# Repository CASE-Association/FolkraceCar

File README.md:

# CASE Folkrace Car - laZEr

## The 2020 Folkrace car project
 A car developed for the main focus of evaluationg, methos for producing a fun and educational car for the Robot SM Folkrace class.
 These are the main topics:
- Navigation
- Mapping/ localisation
- Electric design
- Cassis design
- Weight optimization

## Project Structure

## Placeholder

## System overview

## How do you use it?

## How does it work?

## Development

## Contributors

## License

Distributed under the MIT license. See ``LICENSE`` for more information.

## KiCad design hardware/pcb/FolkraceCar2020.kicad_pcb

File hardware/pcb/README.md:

## Notes for Folkrace PCB

### Bring up notes for REV 1-2

* eFuse does not work consistently - two have been broken - unclear why

#### Changes for next rev

* Add way to connect external 5V (protection for DC/DC)
* On off for 3V3 (complete rail)
* Move to edge-mounted buttons
* Check real width of screen (38 mm length)
* Reconnect fault LED to not be on when off
* Change to better switch for on/off operation
* Transient protection and possibly reverse current diode for eFuse
* Check if we can change to Molex nano fit connectors (both connectors oriented towards RP conn)
* Add 90 deg connector for start module
* Flip FAN connector so silkscreen looks good

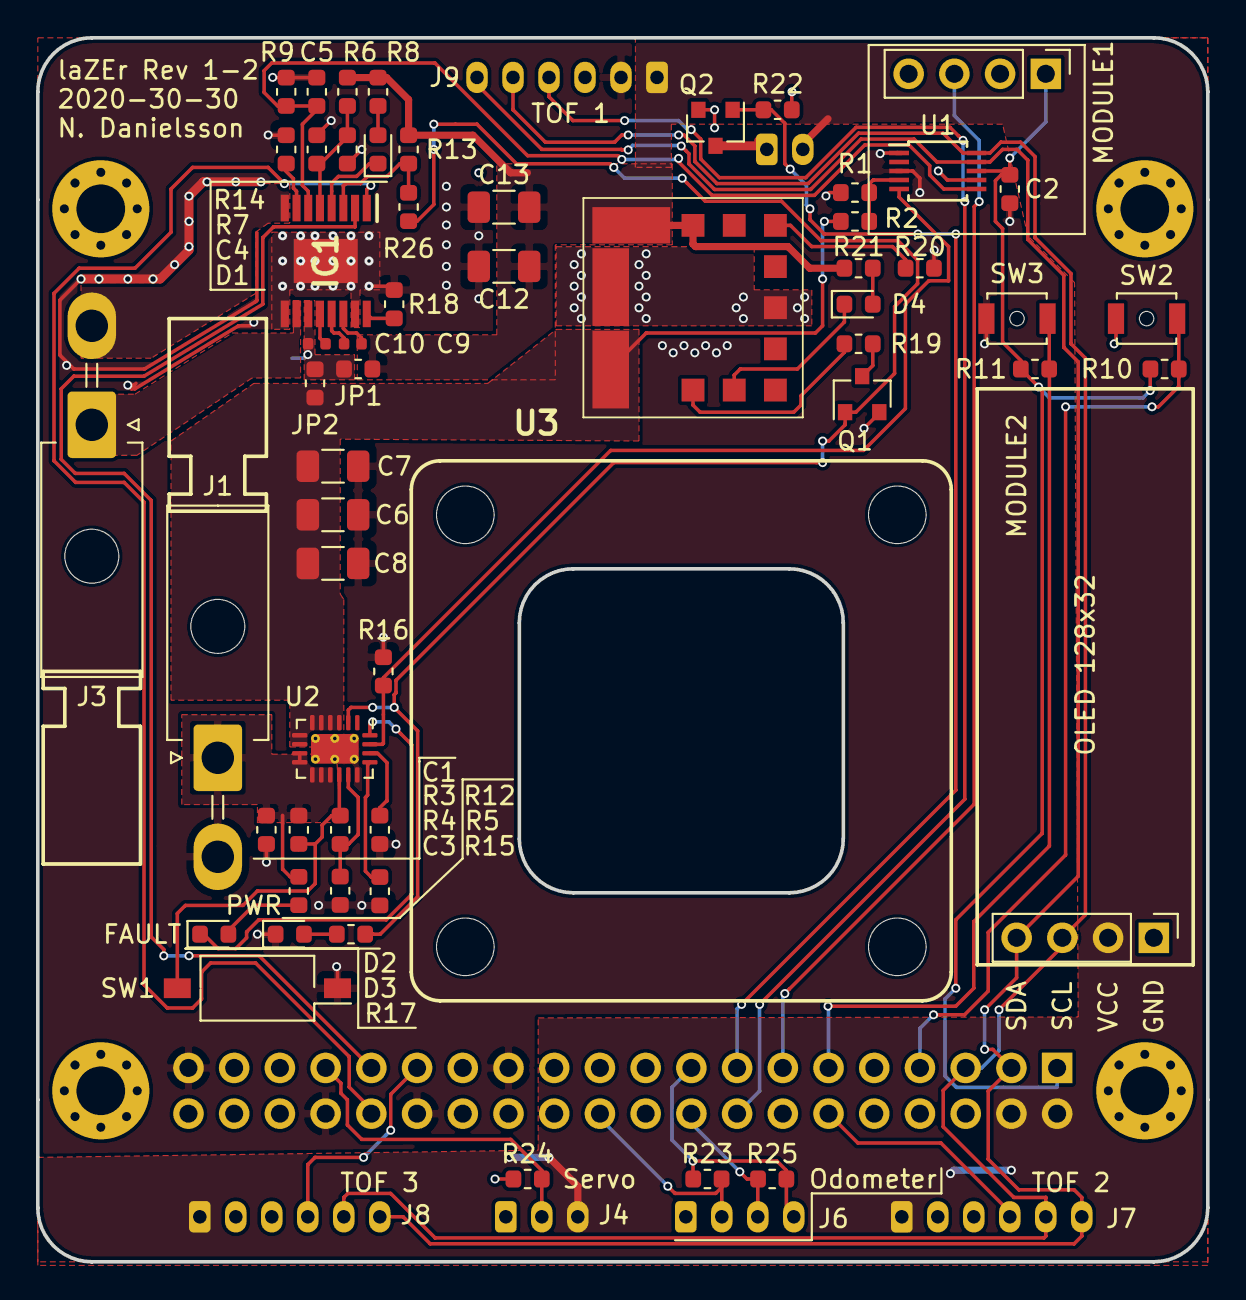
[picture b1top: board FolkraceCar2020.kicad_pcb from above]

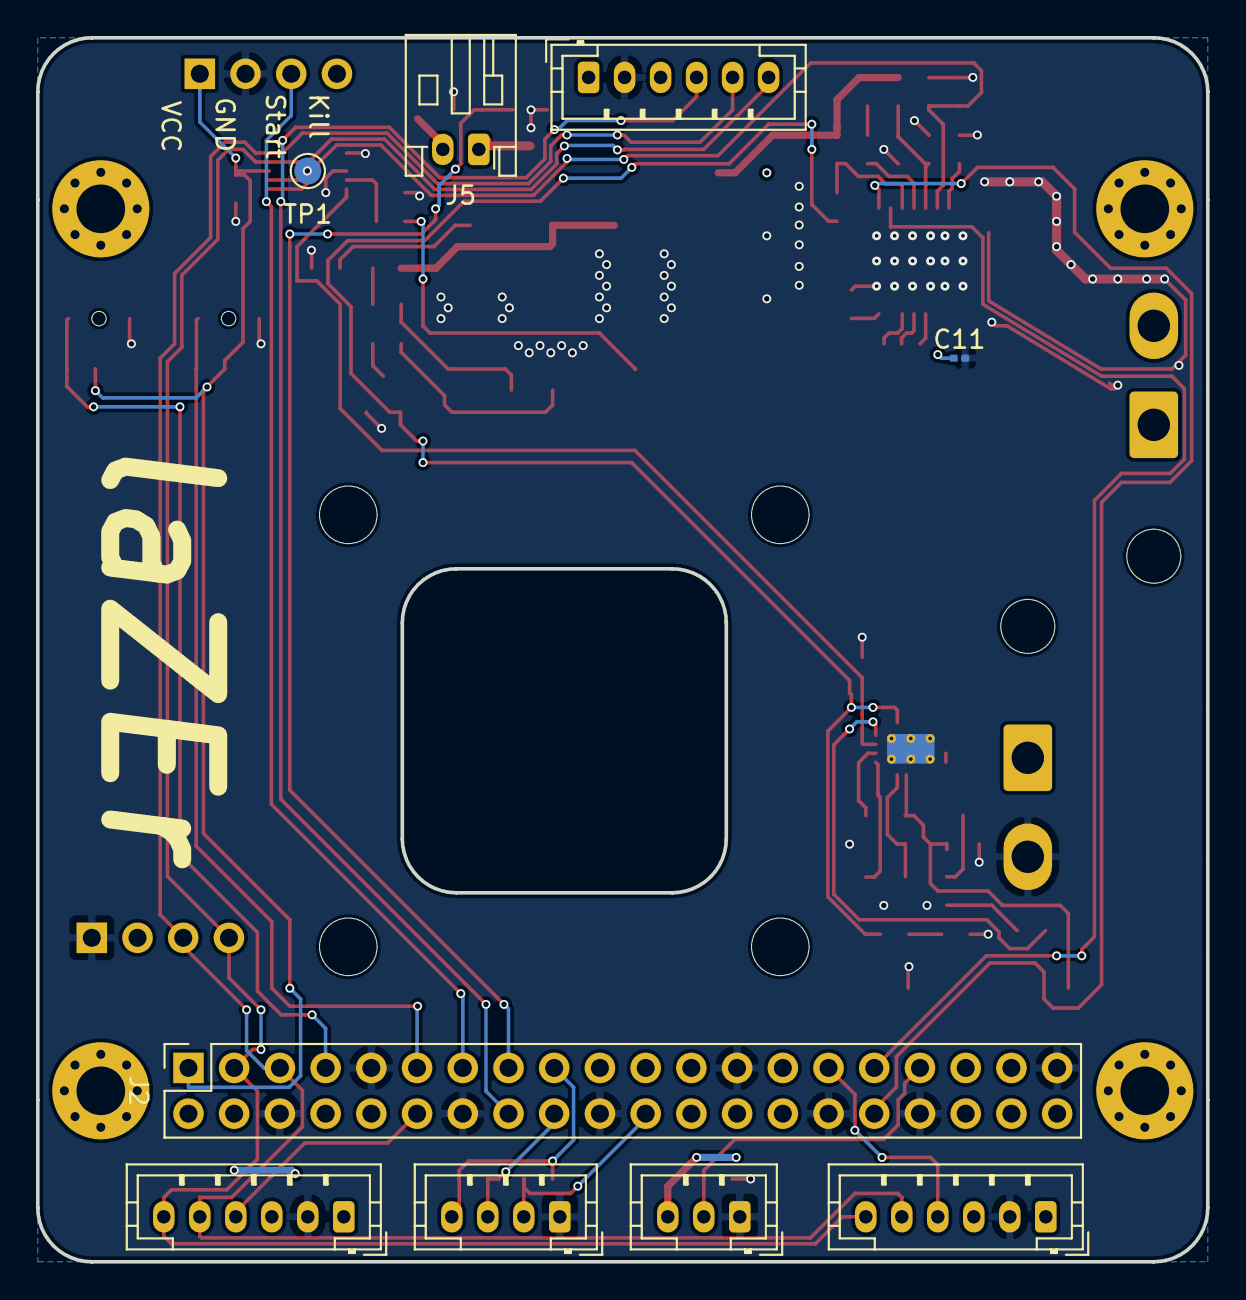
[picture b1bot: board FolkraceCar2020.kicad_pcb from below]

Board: 2 copper layers, 65.0 x 68.0 mm, 74 parts (9 on the bottom side), 49 nets.

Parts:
C1, C2, C3, C4, C5: C; C_0603_1608Metric
C6, C7, C8, C12, C13: C; C_1206_3216Metric
C9: 22nF X7R > 16 V; C_0402_1005Metric
C10: 100nF X7R > 16 V; C_0402_1005Metric
C11: 100nF X7R > 16 V; C_0201_0603Metric
D1, D2: LED RED; LED_0603_1608Metric
D3, D4: LED GREEN; LED_0603_1608Metric
H1, H2, H5, H6: MountingHole; MountingHole_3.2mm_M3_ISO7380
H3, H4, H7, H8: MountingHole_Pad; MountingHole_2.7mm_M2.5_Pad_Via
IC1: DRV8874PWPR; SOP65P640X120-17N
J1, J3: Conn_01x02_Male; Molex_Mini-Fit_Jr_5569-02A2_2x01_P4.20mm_Horizontal
J2: Raspberry_Pi; PinSocket_2x20_P2.54mm_Vertical
J4: Conn Servo; JST_PH_B3B-PH-K_1x03_P2.00mm_Vertical
J5: Conn Fan; JST_PH_S2B-PH-K_1x02_P2.00mm_Horizontal
J6: Conn Hall Effect; JST_PH_B4B-PH-K_1x04_P2.00mm_Vertical
J7, J8, J9: Conn_01x06_Male; JST_PH_B6B-PH-K_1x06_P2.00mm_Vertical
JP1, JP2: Jumper; R_0603_1608Metric
MODULE1: Startmodule; PinHeader_1x04_P2.54mm_Vertical
MODULE2: OLED 128x32; PinHeader_1x04_P2.54mm_Vertical
Q1: BSS138; SOT-23
Q2: DMN10H220L; SOT-23
R1, R2, R3, R4, R5, R6, R7, R8, R9, R10, R11, R12, R13, R14, R15, R16, R17, R18, R21, R22, R23, R24, R25, R26: R; R_0603_1608Metric
R19: 0; R_0603_1608Metric
R20: 1.3k; R_0603_1608Metric
SW1: SPST; SW_DIP_SPSTx01_Slide_Omron_A6S-110x_W8.9mm_P2.54mm
SW2, SW3: SW_Push; SW_SPST_B3U-1000P-B
TP1: TestPoint; TestPoint_Pad_D1.5mm
U1: ADS1115IDGS; TSSOP-10_3x3mm_P0.5mm
U2: TPS25940x-Q1; QFN-20-1EP_3x4mm_P0.5mm_EP1.65x2.65mm_ThermalVias
U3: OKL-T_6-W12N-C; OKL2T6W12PC

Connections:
+3V3: C2.1, J2.1, J2.17, J6.4, MODULE1.1, R10.1, R11.1, R23.1, R25.1, U1.8
+5V: C12.1, C13.1, J2.2, J2.4, J4.3, J5.2, J7.1, J8.1, J9.1, JP1.1, MODULE2.2, R6.1, R8.1, R13.2, R21.1, U3.4, U3.5
+BATT: C1.1, J1.1, R3.1, R15.1, U2.9, U2.10, U2.11, U2.12, U2.13
/B1: J2.7, R10.2, SW2.2
/B2: J2.11, R11.2, SW3.2
/DIR_M: IC1.2, J2.31
/FAN-: J5.1, Q2.3
/FAN_CTRL: J2.15, Q2.1, R22.1
/IMON: R16.1, U1.5, U2.19
/IMON_M: C5.2, IC1.6, R9.2, U1.6
/M1: IC1.8, J3.2
/M2: IC1.10, J3.1
/ME_A: J2.18, J6.3, R25.2
/ME_B: J2.22, J6.2, R23.2
/NSLEEP: IC1.3, R13.1, R26.1
/PGOOD: Q1.1, R17.1, R26.2, U2.2
/PWM_M: IC1.1, J2.32
/SCL: J2.5, J7.5, J8.5, J9.5, MODULE2.3, U1.10
/SDA: J2.3, J7.6, J8.6, J9.6, MODULE2.4, U1.9
/SERVO_PWM: J2.33, J4.2, R24.1
/Start: J2.13, MODULE1.3
/VM: C10.2, C11.1, IC1.11, JP1.2, JP2.1
/VMON: R1.2, R2.1, U1.4
/~PGOOD: Q1.3, R19.2
/~SHDN_TOF_1: J2.16, J9.4
/~SHDN_TOF_2: J2.12, J7.4
/~SHDN_TOF_3: J2.29, J8.4
GND: C1.2, C2.2, C3.2, C4.1, C5.1, C6.2, C7.2, C8.2, C11.2, C12.2, C13.2, D3.1, IC1.9, IC1.15, IC1.17, J1.2, J2.6, J2.9, J2.14, J2.20, J2.25, J2.30, J2.34, J2.39, J4.1, J6.1, J7.2, J8.2, J9.2, MODULE1.2, MODULE2.1, Q1.2, Q2.2, R2.2, R5.2, R7.2, R9.1, R12.2, R14.1, R16.2, R18.2, R20.2, R22.2, R24.2, SW1.1, SW2.1, SW3.1, U1.1, U1.3, U2.16, U2.21, U3.3, U3.7
unnamed: C3.1, U2.18
unnamed: C4.2, IC1.5, R6.2, R7.1
unnamed: C9.1, IC1.14
unnamed: C9.2, IC1.13
unnamed: C10.1, IC1.12
unnamed: D1.1, IC1.4
unnamed: D1.2, R8.2
unnamed: D2.1, U2.20
unnamed: D2.2, R15.2
unnamed: D3.2, R17.2
unnamed: D4.1, U3.10
unnamed: D4.2, R21.2
unnamed: IC1.7, R14.2
unnamed: IC1.16, R18.1
unnamed: R3.2, R4.1, SW1.2, U2.14
unnamed: R4.2, R5.1, U2.15
unnamed: R12.1, U2.17
unnamed: R19.1, U3.1
unnamed: R20.1, U3.6
unnamed: TP1.1, U1.7
VBUS: C6.1, C7.1, C8.1, JP2.2, R1.1, U2.3, U2.4, U2.5, U2.6, U2.7, U2.8, U3.2

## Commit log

2020-02-19 update project name
2020-02-20 Create LICENSE
2020-02-21 add realsense example
2020-02-22 add LICENSE for Realsense code
2020-02-22 fix LICENSE
2020-02-22 fix README and add .gitignor
2020-02-23 initial concept code
2020-02-23 improved car model
2020-02-23 init implementation Car handler and Path planner classes
2020-02-23 imp concep ground_plane estimator in path_planner
2020-02-23 migrated Folkracer and PathPlanner code to module folder
2020-02-24 migrated image code to MatrixMagic
2020-02-24 name change
2020-03-01 initial point_cloud concept viewer using cv2
2020-03-07 working concept
2020-03-07 initial working theta-finder using only CPU
2020-03-07 some optimization to theta-finder
2020-03-07 add strin allocating to print
2020-03-08 initial Multiprocessing code
2020-03-08 working multiprocessing theta-finder!
2020-03-09 servo: initial commit
2020-03-10 add script for enabling pwm
2020-03-10 create Servo class and initial testing
2020-03-11 bugfix servo init frequency
2020-03-11 code ready for initial hw test!
2020-03-18 Deleted old folders
2020-03-18 removed
2020-03-18 re-organized folder structure
2020-03-18 test
2020-03-18 test2
2020-03-18 deleted
2020-03-18 added hardware and pcb folder
2020-03-18 added kicad project
2020-03-20 KiCad gitignore file added
2020-03-20 started on schematic design
2020-03-20 Outline added to pcb layout
2020-03-22 updated schematic
2020-03-23 note about hall effect sensor
2020-03-23 fix true FPS
2020-03-23 added link to stackable header
2020-03-23 init framework for video stream
2020-03-24 added todo in schematic
2020-03-24 added lib
2020-03-24 fixed path to symbol lib
2020-03-24 deleted outline
2020-03-24 added new outline and RP connector
2020-03-24 added symbol, footprint and 3d model for DRV8874
2020-03-24 updated footprint
2020-03-26 cleaup
2020-03-28 bugfix and cleanup
2020-03-28 started layout of PCB
2020-03-28 created fan controller
2020-03-28 initial speedcontroller implementation
2020-03-29 extended pcb outline
2020-03-29 worked on pcb layout. Some Schematic def. still to be done
2020-03-29 added redering of RP4 and custom electronics
2020-03-29 Fixed img link error
2020-03-29 changed name to be wo spaces
2020-03-29 Added note about connector problem
2020-03-30 Finished with rev 1
2020-03-30 fixed 3v3 error
2020-03-30 added pdf schematic
2020-03-31 pcb rev 1-2
2020-04-02 Added project name
2020-04-02 updated BOM info in shcematic
2020-04-02 Started on BOM for Mouser order
2020-04-05 Updated Mouser order list and added comment to README
2020-04-06 initial speedcontrol testing
2020-04-07 PI controller w\o direction working
2020-04-07 fix and tuning
2020-04-07 cleanup
2020-04-09 added get_image function to camera class
2020-04-09 major restructure and cleanup
2020-04-09 restructure working
2020-04-09 implemented image extraction
2020-04-09 web server can now show camera stream
2020-04-11 improved WebControl page
2020-04-12 concep WebController implemented
2020-04-12 minor fixes
2020-04-12 Bump typed-ast from 1.3.1 to 1.3.2 in /software/module
    Bumps [typed-ast](https://github.com/python/typed_ast) from 1.3.1 to 1.3.2.
    - [Release notes](https://github.com/python/typed_ast/releases)
    - [Changelog](https://github.com/python/typed_ast/blob/master/release_process.md)
    - [Commits](https://github.com/python/typed_ast/compare/1.3.1...1.3.2)
2020-04-12 Bump psutil from 5.5.1 to 5.6.6 in /software/module
    Bumps [psutil](https://github.com/giampaolo/psutil) from 5.5.1 to 5.6.6.
    - [Release notes](https://github.com/giampaolo/psutil/releases)
    - [Changelog](https://github.com/giampaolo/psutil/blob/master/HISTORY.rst)
    - [Commits](https://github.com/giampaolo/psutil/compare/release-5.5.1...release-5.6.6)
2020-04-12 Bump werkzeug from 0.14.1 to 0.15.3 in /software/module
    Bumps [werkzeug](https://github.com/pallets/werkzeug) from 0.14.1 to 0.15.3.
    - [Release notes](https://github.com/pallets/werkzeug/releases)
    - [Changelog](https://github.com/pallets/werkzeug/blob/master/CHANGES.rst)
    - [Commits](https://github.com/pallets/werkzeug/compare/0.14.1...0.15.3)
2020-04-12 Bump pyxdg from 0.25 to 0.26 in /software/module
    Bumps [pyxdg](https://github.com/takluyver/pyxdg) from 0.25 to 0.26.
    - [Release notes](https://github.com/takluyver/pyxdg/releases)
    - [Changelog](https://github.com/takluyver/pyxdg/blob/master/ChangeLog)
    - [Commits](https://github.com/takluyver/pyxdg/compare/rel-0.25...rel-0.26)
2020-04-12 Bump urllib3 from 1.24.1 to 1.24.2 in /software/module
    Bumps [urllib3](https://github.com/urllib3/urllib3) from 1.24.1 to 1.24.2.
    - [Release notes](https://github.com/urllib3/urllib3/releases)
    - [Changelog](https://github.com/urllib3/urllib3/blob/master/CHANGES.rst)
    - [Commits](https://github.com/urllib3/urllib3/compare/1.24.1...1.24.2)
2020-04-15 added notes and values to components
2020-04-17 added updated schematic
2020-04-17 initial code for ADC and Oled
2020-04-24 notes for next rev
2020-10-27 Bump cryptography from 2.6.1 to 3.2 in /software/module
    Bumps [cryptography](https://github.com/pyca/cryptography) from 2.6.1 to 3.2.
    - [Release notes](https://github.com/pyca/cryptography/releases)
    - [Changelog](https://github.com/pyca/cryptography/blob/master/CHANGELOG.rst)
    - [Commits](https://github.com/pyca/cryptography/compare/2.6.1...3.2)
2020-10-27 Bump cryptography from 2.6.1 to 3.2 in /software
    Bumps [cryptography](https://github.com/pyca/cryptography) from 2.6.1 to 3.2.
    - [Release notes](https://github.com/pyca/cryptography/releases)
    - [Changelog](https://github.com/pyca/cryptography/blob/master/CHANGELOG.rst)
    - [Commits](https://github.com/pyca/cryptography/compare/2.6.1...3.2)
2021-01-07 Bump lxml from 4.3.2 to 4.6.2 in /software/module
    Bumps [lxml](https://github.com/lxml/lxml) from 4.3.2 to 4.6.2.
    - [Release notes](https://github.com/lxml/lxml/releases)
    - [Changelog](https://github.com/lxml/lxml/blob/master/CHANGES.txt)
    - [Commits](https://github.com/lxml/lxml/compare/lxml-4.3.2...lxml-4.6.2)
2021-01-07 Bump lxml from 4.3.2 to 4.6.2 in /software
    Bumps [lxml](https://github.com/lxml/lxml) from 4.3.2 to 4.6.2.
    - [Release notes](https://github.com/lxml/lxml/releases)
    - [Changelog](https://github.com/lxml/lxml/blob/master/CHANGES.txt)
    - [Commits](https://github.com/lxml/lxml/compare/lxml-4.3.2...lxml-4.6.2)
2021-03-19 Bump pillow from 5.4.1 to 8.1.1 in /software/module
    Bumps [pillow](https://github.com/python-pillow/Pillow) from 5.4.1 to 8.1.1.
    - [Release notes](https://github.com/python-pillow/Pillow/releases)
    - [Changelog](https://github.com/python-pillow/Pillow/blob/master/CHANGES.rst)
    - [Commits](https://github.com/python-pillow/Pillow/compare/5.4.1...8.1.1)
2021-03-19 Bump pillow from 5.4.1 to 8.1.1 in /software
    Bumps [pillow](https://github.com/python-pillow/Pillow) from 5.4.1 to 8.1.1.
    - [Release notes](https://github.com/python-pillow/Pillow/releases)
    - [Changelog](https://github.com/python-pillow/Pillow/blob/master/CHANGES.rst)
    - [Commits](https://github.com/python-pillow/Pillow/compare/5.4.1...8.1.1)
2021-03-20 Bump jinja2 from 2.10 to 2.11.3 in /software/module
    Bumps [jinja2](https://github.com/pallets/jinja) from 2.10 to 2.11.3.
    - [Release notes](https://github.com/pallets/jinja/releases)
    - [Changelog](https://github.com/pallets/jinja/blob/master/CHANGES.rst)
    - [Commits](https://github.com/pallets/jinja/compare/2.10...2.11.3)
2021-03-20 Bump jinja2 from 2.10 to 2.11.3 in /software
    Bumps [jinja2](https://github.com/pallets/jinja) from 2.10 to 2.11.3.
    - [Release notes](https://github.com/pallets/jinja/releases)
    - [Changelog](https://github.com/pallets/jinja/blob/master/CHANGES.rst)
    - [Commits](https://github.com/pallets/jinja/compare/2.10...2.11.3)
2021-03-29 Bump pygments from 2.3.1 to 2.7.4 in /software/module
    Bumps [pygments](https://github.com/pygments/pygments) from 2.3.1 to 2.7.4.
    - [Release notes](https://github.com/pygments/pygments/releases)
    - [Changelog](https://github.com/pygments/pygments/blob/master/CHANGES)
    - [Commits](https://github.com/pygments/pygments/compare/2.3.1...2.7.4)
2021-03-30 Bump pygments from 2.3.1 to 2.7.4 in /software
    Bumps [pygments](https://github.com/pygments/pygments) from 2.3.1 to 2.7.4.
    - [Release notes](https://github.com/pygments/pygments/releases)
    - [Changelog](https://github.com/pygments/pygments/blob/master/CHANGES)
    - [Commits](https://github.com/pygments/pygments/compare/2.3.1...2.7.4)
2021-03-31 Bump lxml from 4.3.2 to 4.6.3 in /software/module
    Bumps [lxml](https://github.com/lxml/lxml) from 4.3.2 to 4.6.3.
    - [Release notes](https://github.com/lxml/lxml/releases)
    - [Changelog](https://github.com/lxml/lxml/blob/master/CHANGES.txt)
    - [Commits](https://github.com/lxml/lxml/compare/lxml-4.3.2...lxml-4.6.3)
2021-03-31 Bump lxml from 4.3.2 to 4.6.3 in /software
    Bumps [lxml](https://github.com/lxml/lxml) from 4.3.2 to 4.6.3.
    - [Release notes](https://github.com/lxml/lxml/releases)
    - [Changelog](https://github.com/lxml/lxml/blob/master/CHANGES.txt)
    - [Commits](https://github.com/lxml/lxml/compare/lxml-4.3.2...lxml-4.6.3)
